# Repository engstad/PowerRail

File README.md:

# PowerRail
A quick and dirty PCB for a +12V/-7V power supply.

This is just a small KiCad project for yet another small PCB that I need.
It's based on Analog Device's ADP5071 chip.

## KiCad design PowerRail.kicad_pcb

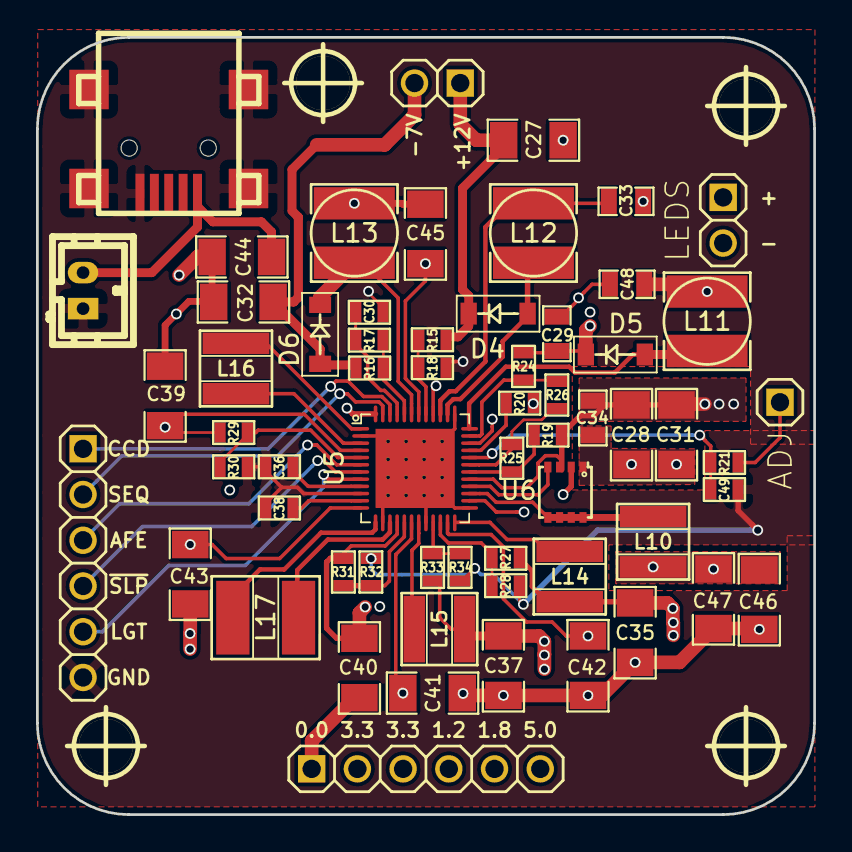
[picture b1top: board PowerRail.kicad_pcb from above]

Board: 4 copper layers, 43.2 x 43.2 mm, 65 parts (0 on the bottom side), 45 nets.

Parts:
C27, C28, C31, C32, C45: 10uF; SM1206
C29, C48: 10uF; SM0805
C30: 1.0u; SM0603
C33: 3.3uF; SM0805
C34: 4.7u; SM0805
C35, C37: 10.0u; SM1206
C36, C38: 0.1u; SM0603
C39, C40: 47.0u; SM1206
C41, C42, C43, C44: 22u; SM1206
C46, C47: 22uF; SM1206
C49: C_Small; SM0603
D4, D5, D6: 30V/0.5A; diode-sod-123
L10, L15: 4.7uH/1.9A; inductor-smd-40x40
L11, L12, L13: 12uH; inductor-smd-4.5x4.5x3.2
L14: 4.7uF/1.0A; inductor-smd-40x40
L16: 4.7uH/1.65A; inductor-smd-40x40
L17: 3.3uH/3.3A; inductor-smd-2020-50x50
P9: ADJ; HDR_1x1
P10: LEDS; HDR_1x2
P11, P14: CONN_01X06; HDR_1x6
P12: CONN_01X02; HDR_1x2
P13: USB_OTG; conn-smd-usb-b-mini
P15: JTI-PWR; b2b-ph-kl
R15: 550k; SM0603
R16: 85.0k; SM0603
R17: 15.0k; SM0603
R18: 50.0k; SM0603
R19: 660k; SM0603
R20: 10; SM0603
R21: 10k; SM0603
R24: 453k; SM0603
R25, R28: 220k; SM0603
R26: 150k; SM0603
R27: 440k; SM0603
R29, R31: 820k; SM0603
R30, R32: 180k; SM0603
R33, R34: 330k; SM0603
U5: TPS65530; qfn-48-p
U6: VEC2616; sot-28fl
hole_3mm, hole_3mm#2, hole_3mm#3, hole_3mm#4: VAL**; hole_3mm

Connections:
/TPS65530/ADJ: P9.1, R21.2
/TPS65530/B-ADJ: C49.1, R21.1, U5.32
/TPS65530/CIN: P10.2, U5.34
/TPS65530/EN_AFE: P14.3, U5.6
/TPS65530/EN_CCD: P14.1, U5.46
/TPS65530/EN_LGT: P14.5, U5.8
/TPS65530/EN_SEQ: P14.2, U5.47
/TPS65530/FB1: R33.1, R34.2, U5.21
/TPS65530/FB2: R31.2, R32.1, U5.17
/TPS65530/FB3: R27.2, R28.1, U5.22
/TPS65530/FB4: R29.2, R30.1, U5.5
/TPS65530/FB6: R16.2, R17.2, U5.44
/TPS65530/FB8: R19.1, R25.2, U5.30
/TPS65530/FBC: R20.1, U5.33
/TPS65530/FBG78: R25.1, R26.1, U5.31
/TPS65530/FBV: R24.2, R26.2, U5.35
/TPS65530/LL8: L10.2, U5.27, U6.5, U6.6, U6.7, U6.8
/TPS65530/REF: C38.2, U5.11
/TPS65530/S56: C30.2, R17.1, U5.45
/TPS65530/SS: C36.2, U5.9
/TPS65530/SW1: L15.1, U5.19
/TPS65530/SW2I: L17.2, U5.15
/TPS65530/SW2S: L17.1, U5.13
/TPS65530/SW4I: L16.2, U5.3
/TPS65530/SW4S: L16.1, U5.1
/TPS65530/SW5: D4.2, L12.2, U5.38
/TPS65530/SW6: D6.1, L13.1, U5.43
/TPS65530/SW7: D5.2, L11.2, U5.36
/TPS65530/SW8HD: U5.28, U6.4
/TPS65530/SW8LD: U5.26, U6.2
/TPS65530/SWOUT: C33.1, L12.1, U5.39
/TPS65530/VBATT: C41.1, C42.1, C43.1, C44.1, C45.2, C46.1, C47.1, C48.2, L10.1, L11.1, P13.1, P15.2, U5.12, U5.18, U5.23, U5.40, U5.42, U5.48
/TPS65530/VOUT_AFE_3V3: C39.1, P11.2, R29.1, U5.4
/TPS65530/VOUT_BACKL_5V: C29.1, D5.1, P10.1, R24.1
/TPS65530/VOUT_CCD+: C27.1, D4.1, P12.1, R15.2
/TPS65530/VOUT_CCD-: C32.2, D6.2, P12.2, R16.1
/TPS65530/VOUT_CORE_1V2: C37.1, L15.2, P11.4, R33.2
/TPS65530/VOUT_IO_3V3: C40.1, P11.3, R31.1, U5.16
/TPS65530/VOUT_MEM_1V8: C35.2, L14.2, P11.5, R27.1
/TPS65530/VOUT_MOTOR_5V: C28.1, C31.1, C34.1, P11.6, R19.2, U5.29, U6.3
/TPS65530/XSLEEP: P14.4, U5.7
GND: C30.1, C36.1, C38.1, C49.2, P13.5, P13.6, P14.6, P15.1, R18.2, R28.2, R30.2, R32.2, R34.1, U5.10
GNDPWR: C27.2, C28.2, C29.2, C31.2, C32.1, C33.2, C34.2, C35.1, C37.2, C39.2, C40.2, C41.2, C42.2, C43.2, C44.2, C45.1, C46.2, C47.2, C48.1, L13.2, P11.1, R20.2, U5.2, U5.14, U5.20, U5.25, U5.37, U5.49, U6.1
unnamed: L14.1, U5.24
unnamed: R15.1, R18.1, U5.41

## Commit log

2015-08-12 Add standard .gitignore
2015-08-12 Initial commit.
2015-08-13 Slight changes. Note: Need to add a net-tie
2015-08-13 More work
2015-08-13 Try jpg
2015-08-13 Change wire sizes
2015-08-13 Add image
2015-09-17 More investigations and calculations
2015-11-04 Latest dabbling
2015-11-09 Latest work
2015-11-09 latest at work
2015-11-16 Latest power stuff
2015-11-27 submodule repo change
2015-11-27 Actually, use github
2015-11-28 Follow ADISimPower recommendations
2015-11-28 Adding support docs
2015-11-28 lib sync
2015-11-28 Some change
2015-12-02 Fixes
2015-12-02 update libs
2015-12-21 Tiny fixes
2020-10-23 Safety checkin.
2024-01-12 Upgrade to latest KiCad.
